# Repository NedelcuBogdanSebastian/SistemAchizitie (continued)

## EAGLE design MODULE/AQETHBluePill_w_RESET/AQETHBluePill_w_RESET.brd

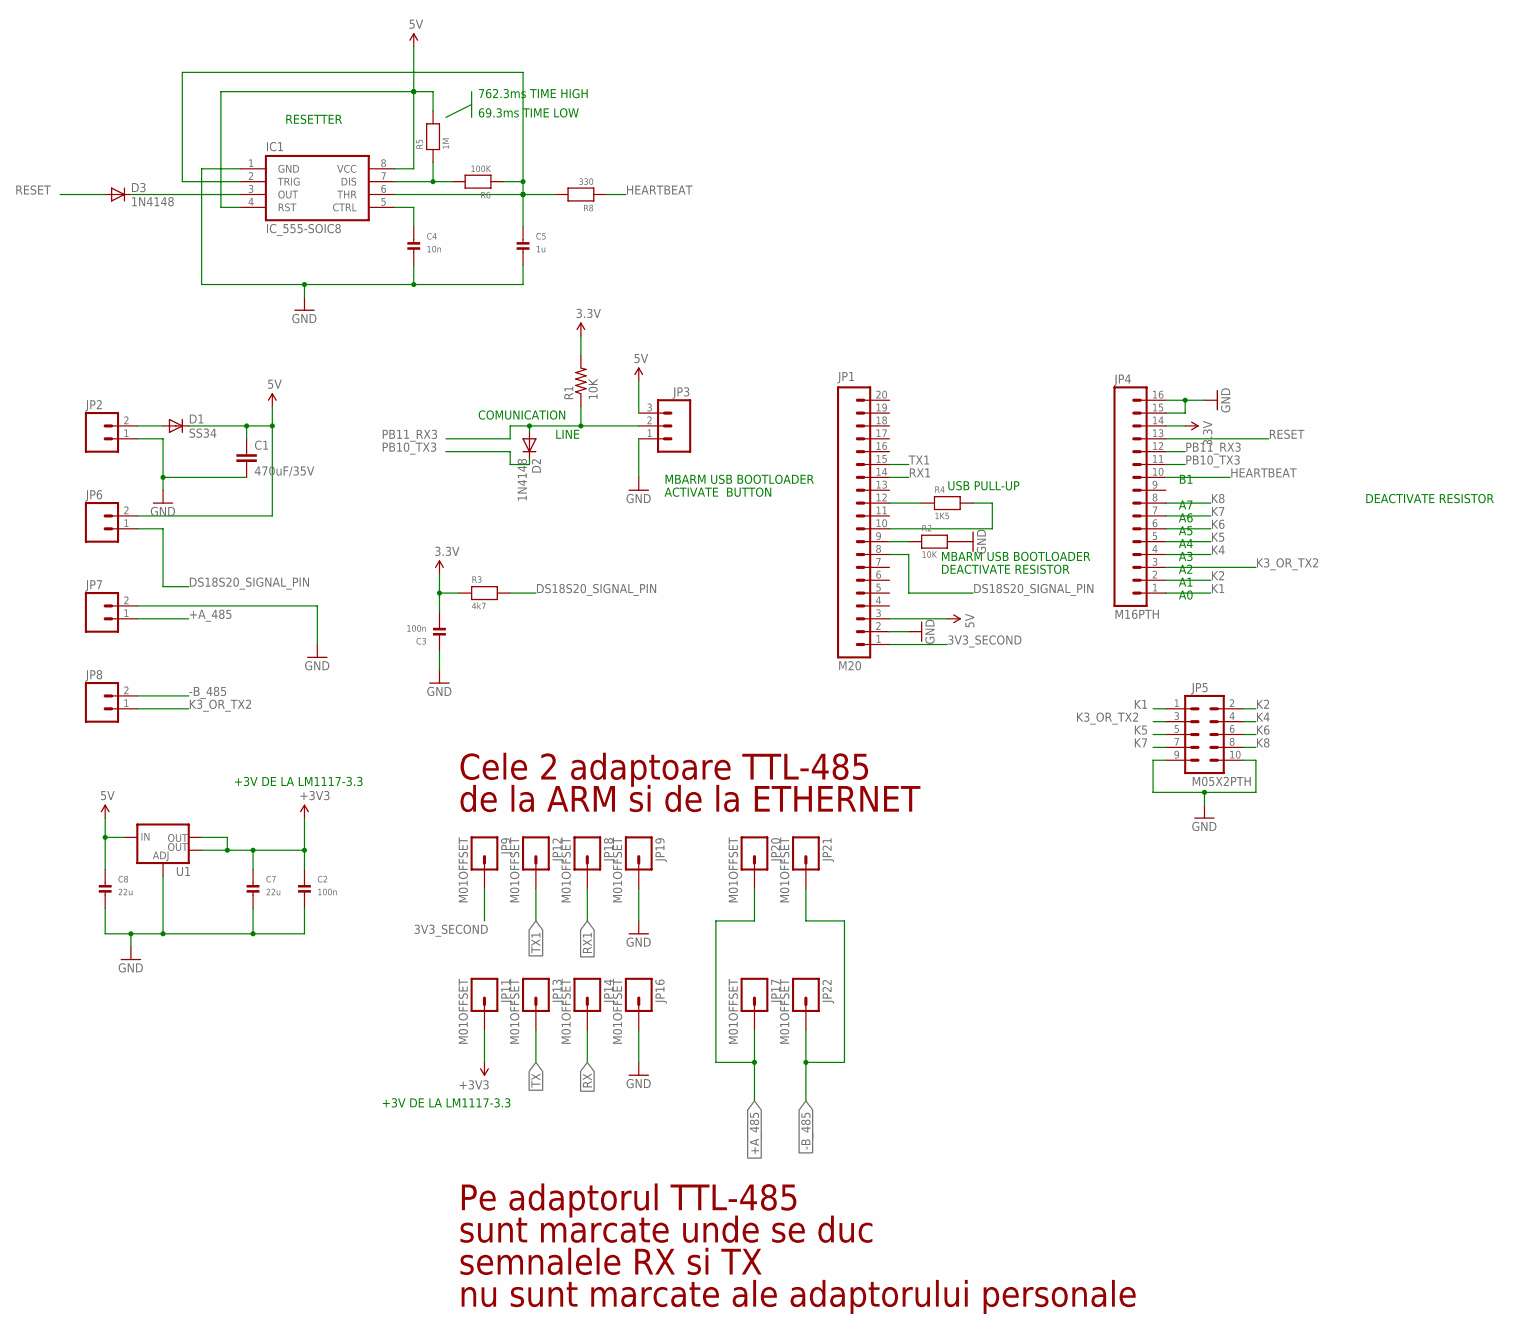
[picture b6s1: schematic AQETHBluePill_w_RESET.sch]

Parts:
C1: 470uF/35V; CAP-PTH-5MM
C2, C3: 100n; _0805MP
C4: 10n; _0805MP
C5: 1u; 1206
C7, C8: 22u; 1206
D1: SS34; SMC
D2, D3: 1N4148; MINIMELF
IC1: IC_555-SOIC8; SOIC-8
JP1: M20; 1X20
JP2, JP6, JP7, JP8: M025MM; SCREWTERMINAL-5MM-2
JP3: M03LOCK_LONGPADS; 1X03_LOCK_LONGPADS
JP4: M16PTH; 1X16
JP5: M05X2PTH; AVR_ICSP
JP9, JP11, JP12, JP13, JP14, JP16, JP17, JP18, JP19, JP20, JP21, JP22: M01OFFSET; 1X01_OFFSET
R1: 10K; 1206
R2: 10K; _0805MP
R3: 4k7; _0805MP
R4: 1K5; _0805MP
R5: 1M; _0805MP
R6: 100K; _0805MP
R8: 330; _0805MP
U1: V_REG_LM1117SOT223; SOT223

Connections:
3.3V: C3.2, JP4.14, R1.2, R3.1
3V3_SECOND: JP1.1, JP9.1
5V: C1.1, C8.1, D1.C, IC1.4 (RST), IC1.8 (VCC), JP1.3, JP3.3, JP6.2, R5.2, U1.3 (IN)
+A_485: JP7.1, JP17.1, JP20.1
-B_485: JP8.2, JP21.1, JP22.1
CTRL: C4.1, IC1.5 (CTRL)
DS18S20_SIGNAL_PIN: JP1.8, JP6.1, R3.2
GND: C1.2, C2.2, C3.1, C4.2, C5.2, C7.2, C8.2, IC1.1 (GND), JP1.2, JP2.1, JP3.1, JP4.15, JP4.16, JP5.9, JP5.10, JP7.2, JP16.1, JP19.1, R2.2, U1.1 (ADJ)
HEARTBEAT: JP4.10, R8.1
K1: JP4.1, JP5.1
K2: JP4.2, JP5.2
K3_OR_TX2: JP4.3, JP5.3, JP8.1
K4: JP4.4, JP5.4
K5: JP4.5, JP5.5
K6: JP4.6, JP5.6
K7: JP4.7, JP5.7
K8: JP4.8, JP5.8
unnamed: JP1.10, R4.2
unnamed: JP1.9, R2.1
unnamed: JP1.12, R4.1
unnamed: C5.1, IC1.2 (TRIG), IC1.6 (THR), R6.1, R8.2
unnamed: D3.C, IC1.3 (OUT)
unnamed: IC1.7 (DIS), R5.1, R6.2
unnamed: D1.A, JP2.2
PB10_TX3: D2.C, JP4.11
PB11_RX3: D2.A, JP3.2, JP4.12, R1.1
RESET: D3.A, JP4.13
RX: JP14.1
RX1: JP1.14, JP18.1
TX: JP13.1
TX1: JP1.15, JP12.1
VCC: C2.1, C7.1, JP11.1, U1.2 (OUT), U1.4 (OUT)

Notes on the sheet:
COMUNICATION
LINE
Pe adaptorul TTL-485
sunt marcate unde se duc
semnalele RX si TX
nu sunt marcate ale adaptorului personale
+3V DE LA LM1117-3.3
Cele 2 adaptoare TTL-485
de la ARM si de la ETHERNET
USB PULL-UP
MBARM USB BOOTLOADER
DEACTIVATE RESISTOR
ACTIVATE BUTTON
69.3ms TIME LOW
762.3ms TIME HIGH
RESETTER

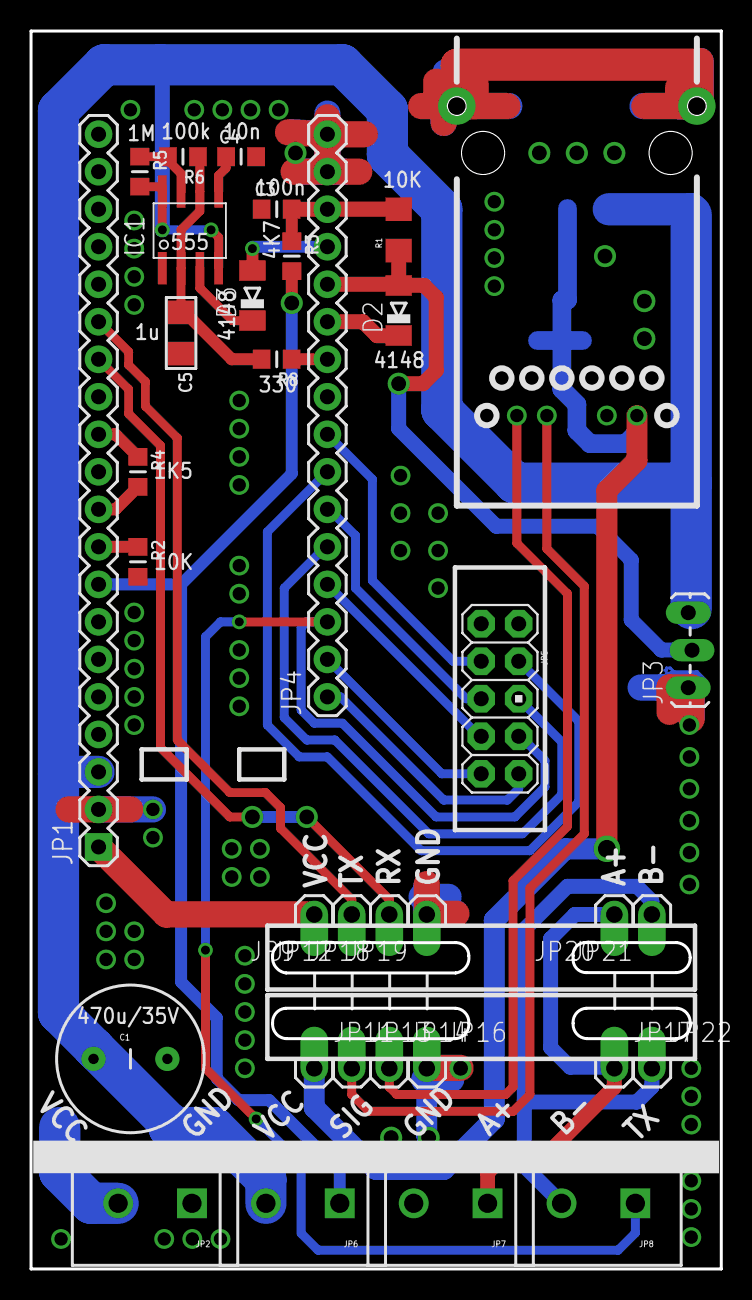
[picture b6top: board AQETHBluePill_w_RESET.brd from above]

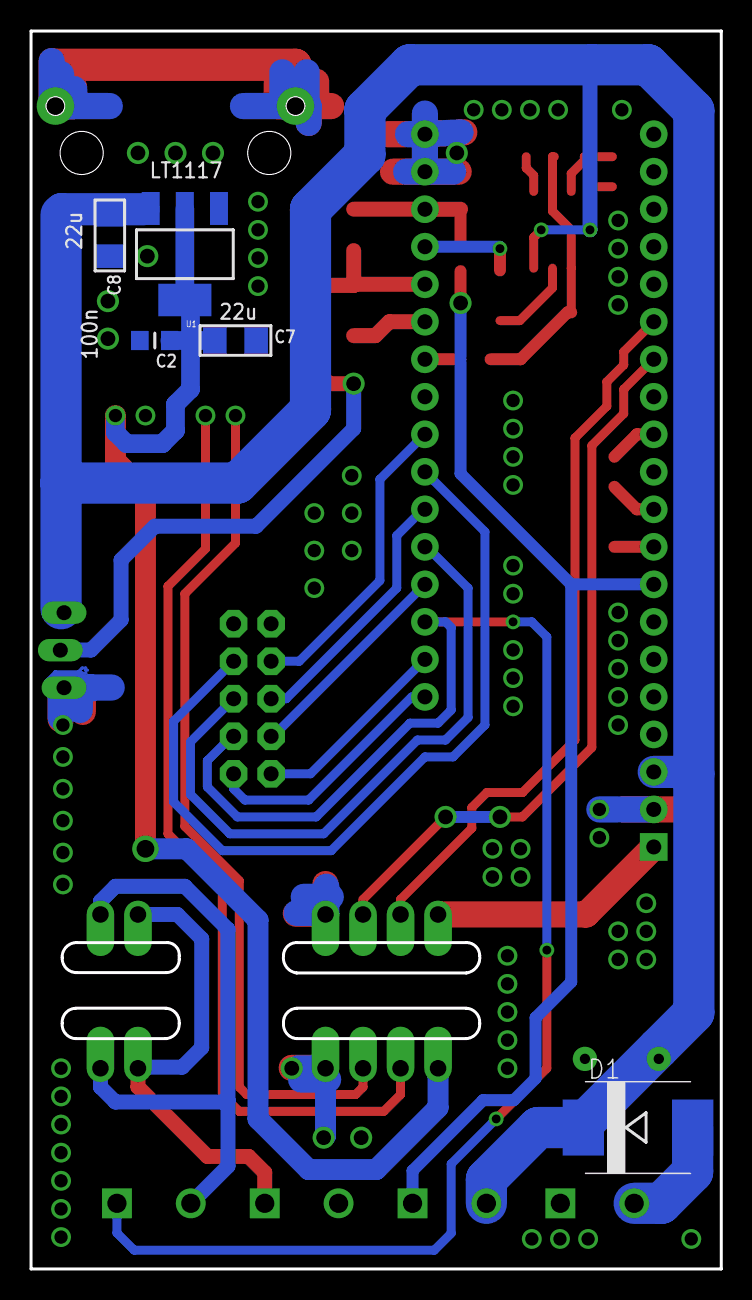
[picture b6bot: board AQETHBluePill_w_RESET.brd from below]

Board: 2 copper layers, 46.7 x 83.8 mm, 39 parts (5 on the bottom side), 30 nets.

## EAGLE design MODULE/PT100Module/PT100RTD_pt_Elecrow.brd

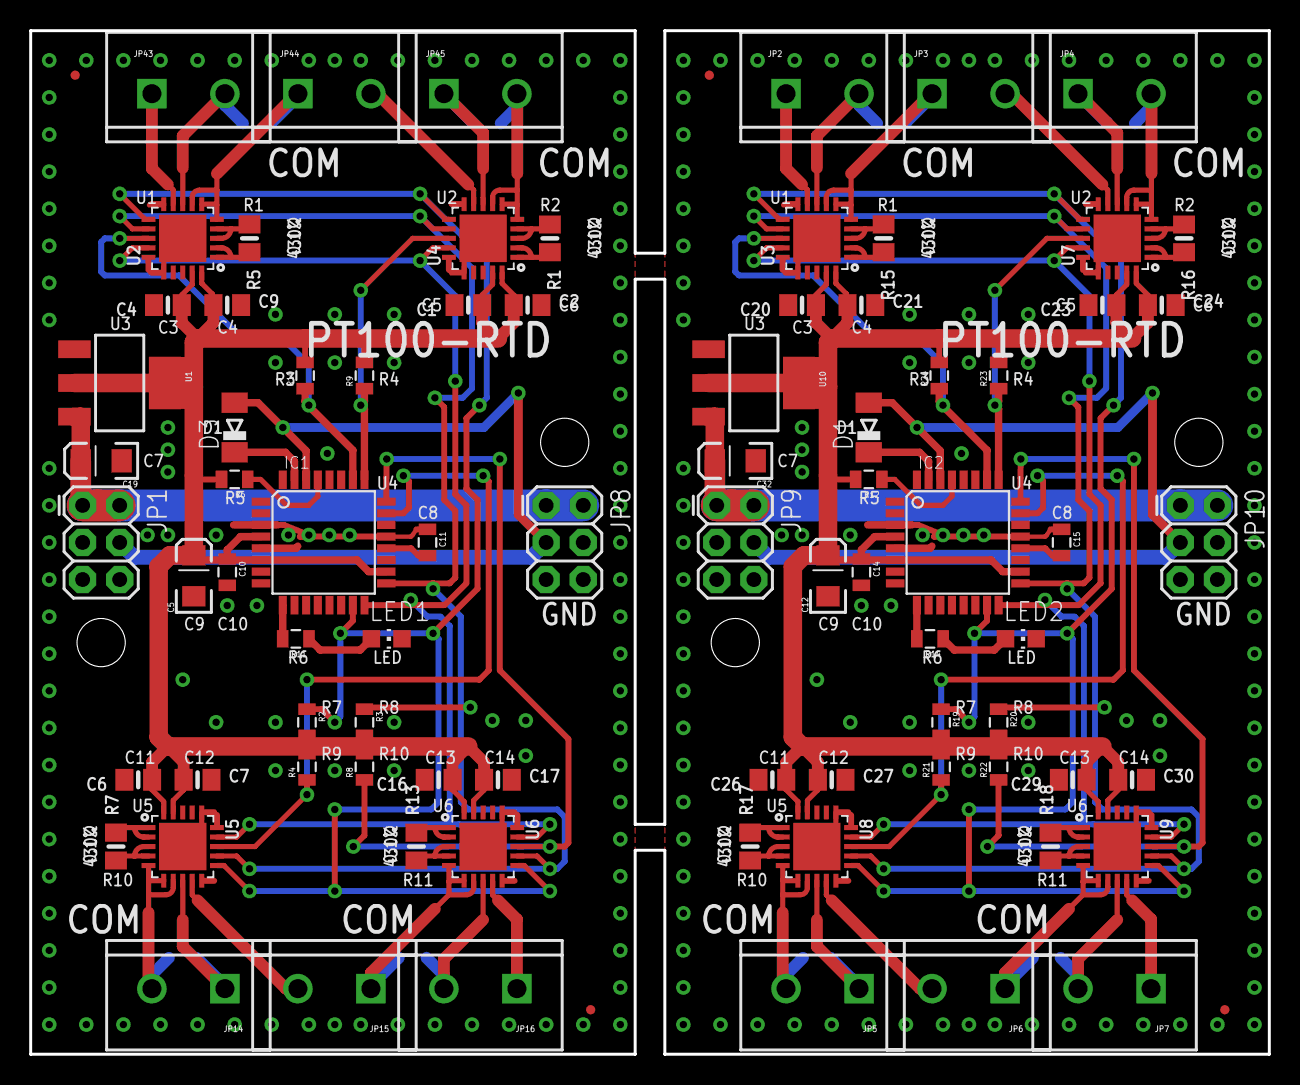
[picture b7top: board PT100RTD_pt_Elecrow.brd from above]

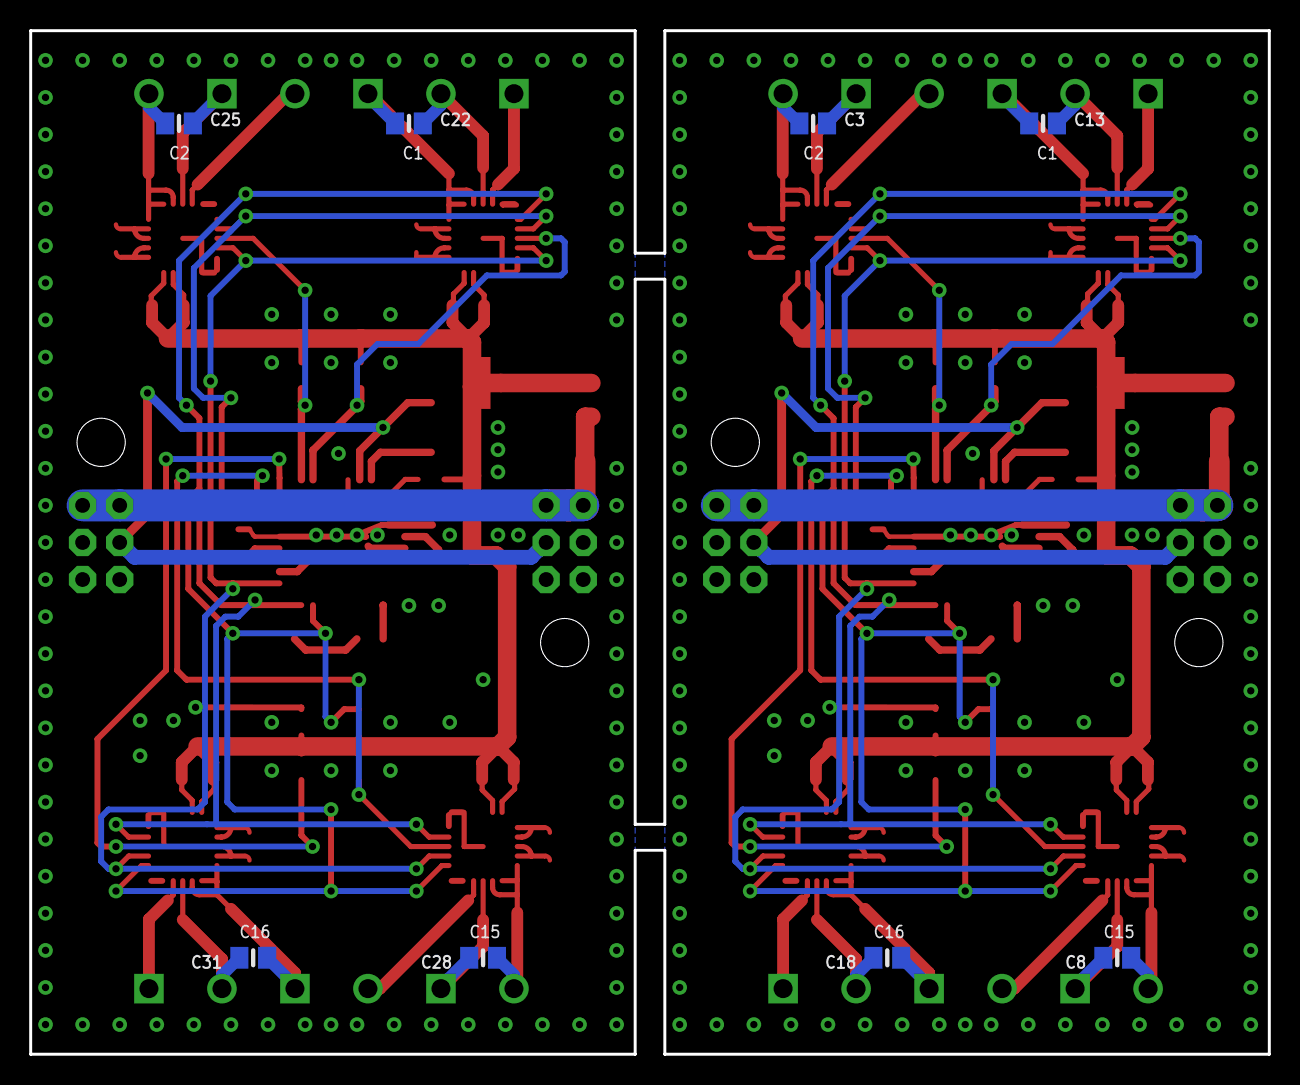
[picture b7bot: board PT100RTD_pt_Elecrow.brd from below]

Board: 2 copper layers, 84.8 x 70.1 mm, 96 parts (8 on the bottom side), 72 nets.

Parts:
C1, C2, C4, C6, C7, C9, C16, C17, C20, C21, C23, C24, C26, C27, C29, C30: 0.1uF; 0805-NO
C3, C8, C13, C18, C22, C25, C28, C31: 100nF; 0805-NO
C5, C12, C19, C32: 22uF/16V; EIA3216
C10, C11, C14, C15: 100n; 0805
D1, D3: 1N4148; MINIMELF
FD1, FD2, FD3, FD4: FIDUCIALUFIDUCIAL; FIDUCIAL-MICRO
IC1, IC2: MEGA8-AI; TQFP32-08
JP1, JP8, JP9, JP10: 2X3
JP2, JP3, JP4, JP5, JP6, JP7, JP14, JP15, JP16, JP43, JP44, JP45: SCREWTERMINAL-5MM-2
LED1, LED2: CHIP-LED0805
R1, R5, R7, R13, R15, R16, R17, R18: 430Ω/0.1%; 0805-NO
R2, R3, R4, R6, R8, R9, R10, R12, R19, R20, R21, R22, R23, R24: 10K; 0805
R11, R14: 0805
STANDOFF1, STANDOFF2, STANDOFF3, STANDOFF4: STAND-OFF
U1, U10: SOT223
U2, U3, U4, U5, U6, U7, U8, U9: MAX31865; QFN20_4MM_0.65MM

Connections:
5V: C19.A, JP1.1, JP1.2, JP8.1, JP8.2, U1.3
5V1: C32.A, JP9.1, JP9.2, JP10.1, JP10.2, U10.3
COM1: D3.A, IC1.30, JP1.4, JP8.3
COM2: D1.A, IC2.30, JP9.4, JP10.3
CS1: IC1.26, R10.1, U2.13
CS2: IC1.25, R9.1, U4.13
CS3: IC1.23, R4.1, U5.13
CS4: IC1.24, R8.1, U6.13
CS5: IC2.26, R24.1, U3.13
CS6: IC2.25, R23.1, U7.13
CS7: IC2.23, R21.1, U8.13
CS8: IC2.24, R22.1, U9.13
GND: C1.2, C2.2, C4.2, C5.C, C6.2, C7.2, C9.2, C10.2, C11.1, C16.2, C17.2, C19.C, IC1.3, IC1.5, IC1.21, JP1.5, JP1.6, JP8.5, JP8.6, LED1.C, U1.1, U2.10, U2.15, U2.16, U2.PAD, U4.10, U4.15, U4.16, U4.PAD, U5.10, U5.15, U5.16, U5.PAD, U6.10, U6.15, U6.16, U6.PAD
GND4: C12.C, C14.2, C15.1, C20.2, C21.2, C23.2, C24.2, C26.2, C27.2, C29.2, C30.2, C32.C, IC2.3, IC2.5, IC2.21, JP9.5, JP9.6, JP10.5, JP10.6, LED2.C, U3.10, U3.15, U3.16, U3.PAD, U7.10, U7.15, U7.16, U7.PAD, U8.10, U8.15, U8.16, U8.PAD, U9.10, U9.15, U9.16, U9.PAD, U10.1
MISO: IC1.16, U2.14, U4.14, U5.14, U6.14
MISO1: IC2.16, U3.14, U7.14, U8.14, U9.14
MOSI: IC1.15, R2.1, U2.11, U4.11, U5.11, U6.11
MOSI1: IC2.15, R19.1, U3.11, U7.11, U8.11, U9.11
unnamed: LED1.A, R11.1
unnamed: D3.C, IC1.31
unnamed: R5.2, U2.1, U2.2
unnamed: R5.1, U2.3, U2.4
unnamed: C11.2, IC1.20
unnamed: R1.2, U4.1, U4.2
unnamed: R1.1, U4.3, U4.4
unnamed: C15.2, IC2.20
unnamed: R7.2, U5.1, U5.2
unnamed: R7.1, U5.3, U5.4
unnamed: IC1.9, R11.2
unnamed: LED2.A, R14.1
unnamed: R13.2, U6.1, U6.2
unnamed: R13.1, U6.3, U6.4
unnamed: D1.C, IC2.31
unnamed: R15.2, U3.1, U3.2
unnamed: R15.1, U3.3, U3.4
unnamed: R16.2, U7.1, U7.2
unnamed: R16.1, U7.3, U7.4
unnamed: R17.2, U8.1, U8.2
unnamed: R17.1, U8.3, U8.4
unnamed: R18.2, U9.1, U9.2
unnamed: R18.1, U9.3, U9.4
unnamed: IC2.9, R14.2
RESET: IC1.29, R6.1
RESET1: IC2.29, R12.1
SCK: IC1.17, R3.1, U2.12, U4.12, U5.12, U6.12
SCK1: IC2.17, R20.1, U3.12, U7.12, U8.12, U9.12
T1A: C13.1, JP44.1, U2.5, U2.6, U2.7
T1A1: C22.1, JP3.1, U3.5, U3.6, U3.7
T1B: C13.2, JP43.2, U2.8
T1B1: C22.2, JP2.2, U3.8
T1C: JP43.1, U2.9
T1C1: JP2.1, U3.9
T2A: C3.1, JP45.2, U4.5, U4.6, U4.7
T2A1: C25.1, JP4.2, U7.5, U7.6, U7.7
T2B: C3.2, JP45.1, U4.8
T2B1: C25.2, JP4.1, U7.8
T2C: JP44.2, U4.9
T2C1: JP3.2, U7.9
T3A: C8.1, JP14.2, U5.5, U5.6, U5.7
T3A1: C28.1, JP5.2, U8.5, U8.6, U8.7
T3B: C8.2, JP14.1, U5.8
T3B1: C28.2, JP5.1, U8.8
T3C: JP15.2, U5.9
T3C1: JP6.2, U8.9
T4A: C18.1, JP15.1, U6.5, U6.6, U6.7
T4A1: C31.1, JP6.1, U9.5, U9.6, U9.7
T4B: C18.2, JP16.2, U6.8
T4B1: C31.2, JP7.2, U9.8
T4C: JP16.1, U6.9
T4C1: JP7.1, U9.9
VCC: C1.1, C2.1, C4.1, C5.A, C6.1, C7.1, C9.1, C10.1, C16.1, C17.1, IC1.4, IC1.6, IC1.18, R2.2, R3.2, R4.2, R6.2, R8.2, R9.2, R10.2, U1.2, U1.4, U2.19, U2.20, U4.19, U4.20, U5.19, U5.20, U6.19, U6.20
VCC1: C12.A, C14.1, C20.1, C21.1, C23.1, C24.1, C26.1, C27.1, C29.1, C30.1, IC2.4, IC2.6, IC2.18, R12.2, R19.2, R20.2, R21.2, R22.2, R23.2, R24.2, U3.19, U3.20, U7.19, U7.20, U8.19, U8.20, U9.19, U9.20, U10.2, U10.4

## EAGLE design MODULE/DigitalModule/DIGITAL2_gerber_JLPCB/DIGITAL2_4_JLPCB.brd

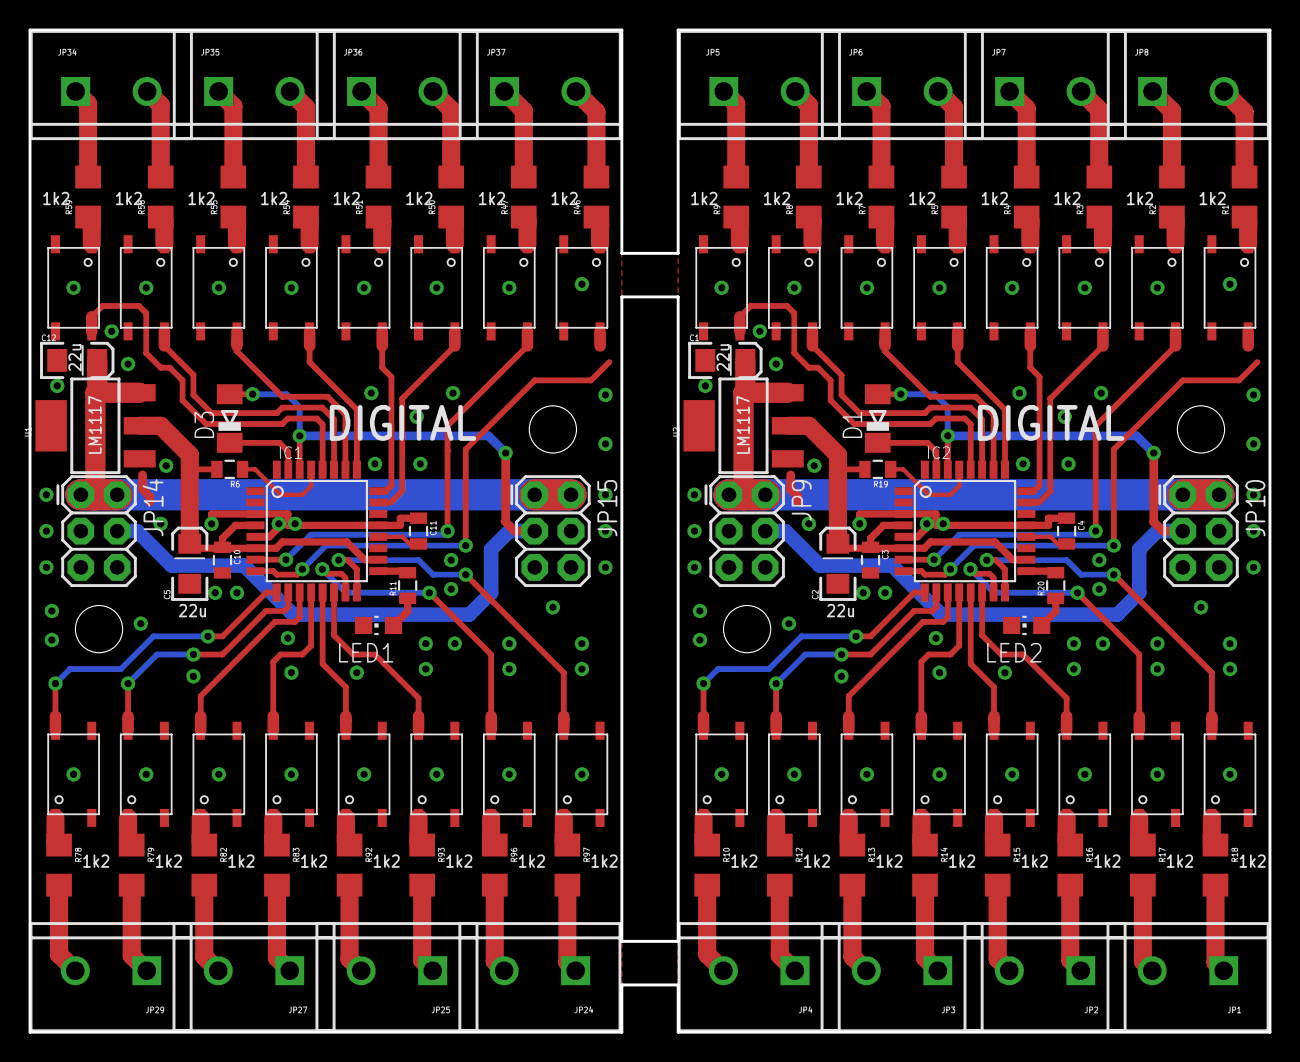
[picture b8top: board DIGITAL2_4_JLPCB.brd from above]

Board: 2 copper layers, 86.7 x 70.1 mm, 108 parts (0 on the bottom side), 114 nets.

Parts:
C1, C2, C5, C12: 22uF/16V; EIA3216
C3, C4, C10, C11: 100n; 0805
D1, D3: 1N4148; MINIMELF
IC1, IC2: MEGA8-AI; TQFP32-08
JP1, JP2, JP3, JP4, JP5, JP6, JP7, JP8, JP24, JP25, JP27, JP29, JP34, JP35, JP36, JP37: SCREWTERMINAL-5MM-2
JP9, JP10, JP14, JP15: 2X3
LED1, LED2: CHIP-LED0805
R1, R2, R3, R4, R5, R7, R8, R9, R10, R12, R13, R14, R15, R16, R17, R18, R46, R47, R50, R51, R54, R55, R58, R59, R78, R79, R82, R83, R92, R93, R96, R97: 1.2K; 1206
R6, R19: 10K; 0805
R11, R20: 0805
STANDOFF1, STANDOFF2, STANDOFF3, STANDOFF4: STAND-OFF
U1, U2: SOT223
U$1, U$2, U$3, U$4, U$5, U$6, U$7, U$8, U$9, U$10, U$11, U$12, U$13, U$14, U$15, U$16, U$17, U$18, U$19, U$20, U$21, U$22, U$23, U$24, U$29, U$30, U$31, U$32, U$33, U$34, U$35, U$36: IS181D-I; TLP181-I

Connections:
5V: C12.A, JP14.1, JP14.2, JP15.1, JP15.2, U1.3
5V1: C1.A, JP9.1, JP9.2, JP10.1, JP10.2, U2.3
COM1: D3.A, IC1.30, JP14.4, JP15.3
COM3: D1.A, IC2.30, JP9.4, JP10.3
D1: IC2.9, U$9.P$4
D2: IC2.10, U$10.P$4
D3: IC1.8, U$13.P$4
D4: IC1.7, U$14.P$4
D5: IC1.23, U$15.P$4
D6: IC1.24, U$16.P$4
D7: IC1.25, U$17.P$4
D8: IC1.26, U$18.P$4
D9: IC1.27, U$19.P$4
D10: IC1.28, U$20.P$4
D11: IC1.9, U$29.P$4
D12: IC1.10, U$30.P$4
D13: IC1.11, U$31.P$4
D14: IC1.12, U$32.P$4
D15: IC1.13, U$33.P$4
D16: IC1.14, U$34.P$4
D17: IC1.15, U$35.P$4
D18: IC1.16, U$36.P$4
D19: IC2.11, U$11.P$4
D20: IC2.12, U$12.P$4
D21: IC2.13, U$21.P$4
D22: IC2.14, U$22.P$4
D23: IC2.15, U$23.P$4
D24: IC2.16, U$24.P$4
D25: IC2.8, U$1.P$4
D26: IC2.7, U$2.P$4
D27: IC2.23, U$3.P$4
D28: IC2.24, U$4.P$4
D29: IC2.25, U$5.P$4
D30: IC2.26, U$6.P$4
D31: IC2.27, U$7.P$4
D32: IC2.28, U$8.P$4
GND: C5.C, C10.2, C11.1, C12.C, IC1.3, IC1.5, IC1.21, JP14.5, JP14.6, JP15.5, JP15.6, LED1.C, U1.1, U$13.P$2, U$13.P$3, U$14.P$2, U$14.P$3, U$15.P$2, U$15.P$3, U$16.P$2, U$16.P$3, U$17.P$2, U$17.P$3, U$18.P$2, U$18.P$3, U$19.P$2, U$19.P$3, U$20.P$2, U$20.P$3, U$29.P$2, U$29.P$3, U$30.P$2, U$30.P$3, U$31.P$2, U$31.P$3, U$32.P$2, U$32.P$3, U$33.P$2, U$33.P$3, U$34.P$2, U$34.P$3, U$35.P$2, U$35.P$3, U$36.P$2, U$36.P$3
GND2: C1.C, C2.C, C3.2, C4.1, IC2.3, IC2.5, IC2.21, JP9.5, JP9.6, JP10.5, JP10.6, LED2.C, U2.1, U$1.P$2, U$1.P$3, U$2.P$2, U$2.P$3, U$3.P$2, U$3.P$3, U$4.P$2, U$4.P$3, U$5.P$2, U$5.P$3, U$6.P$2, U$6.P$3, U$7.P$2, U$7.P$3, U$8.P$2, U$8.P$3, U$9.P$2, U$9.P$3, U$10.P$2, U$10.P$3, U$11.P$2, U$11.P$3, U$12.P$2, U$12.P$3, U$21.P$2, U$21.P$3, U$22.P$2, U$22.P$3, U$23.P$2, U$23.P$3, U$24.P$2, U$24.P$3
unnamed: LED1.A, R11.1
unnamed: JP8.2, R1.2
unnamed: D3.C, IC1.31
unnamed: JP29.2, R78.2
unnamed: C11.2, IC1.20
unnamed: JP27.2, R82.2
unnamed: JP25.2, R92.2
unnamed: JP8.1, R2.2
unnamed: R1.1, U$1.P$1
unnamed: R2.1, U$2.P$1
unnamed: JP24.2, R96.2
unnamed: JP7.2, R3.2
unnamed: JP7.1, R4.2
unnamed: R3.1, U$3.P$1
unnamed: R4.1, U$4.P$1
unnamed: JP6.2, R5.2
unnamed: JP6.1, R7.2
unnamed: R5.1, U$5.P$1
unnamed: R7.1, U$6.P$1
unnamed: JP27.1, R83.2
unnamed: JP5.2, R8.2
unnamed: JP5.1, R9.2
unnamed: JP25.1, R93.2
unnamed: R8.1, U$7.P$1
unnamed: R9.1, U$8.P$1
unnamed: JP4.1, R12.2
unnamed: R10.1, U$9.P$1
unnamed: JP24.1, R97.2
unnamed: R12.1, U$10.P$1
unnamed: R13.1, U$11.P$1
unnamed: R14.1, U$12.P$1
unnamed: R15.1, U$21.P$1
unnamed: R16.1, U$22.P$1
unnamed: R17.1, U$23.P$1
unnamed: R18.1, U$24.P$1
unnamed: JP3.1, R14.2
unnamed: JP2.1, R16.2
unnamed: JP1.1, R18.2
unnamed: JP4.2, R10.2
unnamed: JP3.2, R13.2
unnamed: JP2.2, R15.2
unnamed: JP1.2, R17.2
unnamed: C4.2, IC2.20
unnamed: LED2.A, R20.1
unnamed: D1.C, IC2.31
unnamed: JP37.2, R46.2
unnamed: JP37.1, R47.2
unnamed: R46.1, U$13.P$1
unnamed: R47.1, U$14.P$1
unnamed: JP36.2, R50.2
unnamed: JP36.1, R51.2
unnamed: R50.1, U$15.P$1
unnamed: R51.1, U$16.P$1
unnamed: JP35.2, R54.2
unnamed: JP35.1, R55.2
unnamed: R54.1, U$17.P$1
unnamed: R55.1, U$18.P$1
unnamed: JP34.2, R58.2
unnamed: JP34.1, R59.2
unnamed: R58.1, U$19.P$1
unnamed: R59.1, U$20.P$1
unnamed: JP29.1, R79.2
unnamed: R78.1, U$29.P$1
unnamed: R79.1, U$30.P$1
unnamed: R82.1, U$31.P$1
unnamed: R83.1, U$32.P$1
unnamed: R92.1, U$33.P$1
unnamed: R93.1, U$34.P$1
unnamed: R96.1, U$35.P$1
unnamed: R97.1, U$36.P$1
RESET: IC1.29, R6.1
RESET2: IC2.29, R19.1
SCK: IC1.17, R11.2
SCK2: IC2.17, R20.2
VCC: C5.A, C10.1, IC1.4, IC1.6, IC1.18, R6.2, U1.2, U1.4
VCC2: C2.A, C3.1, IC2.4, IC2.6, IC2.18, R19.2, U2.2, U2.4

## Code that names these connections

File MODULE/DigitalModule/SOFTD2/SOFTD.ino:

/*
 * SOFT DIGITALE
 * 
 * FUSES
 * --------
 * EFUSE = 0xff     // = 0x07
 * HFUSE = 0xde
 * LFUSE = 0xe2
 * 
 */
 
#define ID   "DA9"

#define LEDON    PORTB |= (1<<PB5)
#define LEDOFF   PORTB &= ~(1<<PB5)

#define TO_HEX(i)   (i <= 9 ? '0' + i : 'A' - 10 + i)

uint16_t u16CRC;

String str;

/*
CRC Generation from the MODBUS Specification V1.02: 
1. Load a 16bit register with FFFF hex (all 1’s). Call this the CRC register. 
2. Exclusive OR the first 8bit byte of the message with the low order byte of the 16 bit CRC register, putting the result in the 
CRC register. 
3. Shift the CRC register one bit to the right (toward the LSB), zero filling the MSB. 
Extract and examine the LSB. 
4. (If the LSB was 0): Repeat Step 3 (another shift). 
(If the LSB was 1): Exclusive OR the CRC register with the polynomial value 0xA001 (1010 0000 0000 0001). 
5. Repeat Steps 3 and 4 until 8 shifts have been performed. When this is done, a complete 8bit byte will have been processed. 
6. Repeat Steps 2 through 5 for the next 8bit byte of the message. Continue doing this until all bytes have been processed. 
7. The final content of the CRC register is the CRC value. 
8. When the CRC is placed into the message, its upper and lower bytes must be swapped.
*/
uint16_t crc16_update(uint16_t crc, uint8_t a)
{
  int i;

  crc ^= a;
  for (i = 0; i < 8; ++i)
  {
    if (crc & 1)
      crc = (crc >> 1) ^ 0xA001;
    else
      crc = (crc >> 1);
  }

  return crc;
}

void setup() {
  // initialize serial port
  Serial.begin(19200);

  // led pin as output
  DDRB |= (1<<PB5);
  LEDOFF;

  // activate pull-ups 
  PORTB |= (1<<PB7)|(1<<PB6)|(1<<PB4)|(1<<PB3)|(1<<PB2)|(1<<PB1)|(1<<PB0);  
  PORTC |= (1<<PC5)|(1<<PC4)|(1<<PC3)|(1<<PC2)|(1<<PC1)|(1<<PC0);
  PORTD |= (1<<PD7)|(1<<PD6)|(1<<PD5);   

  // initialize pins as input
  DDRB &= ~((1<<PB7)&(1<<PB6)&(1<<PB4)&(1<<PB3)&(1<<PB2)&(1<<PB1)&(1<<PB0));  
  DDRC &= ~((1<<PC5)&(1<<PC4)&(1<<PC3)&(1<<PC2)&(1<<PC1)&(1<<PC0));
  DDRD &= ~((1<<PD7)&(1<<PD6)&(1<<PD5));
   
  for (int i=0; i < 10; i++)
  {
    delay(30);    
    LEDON;
    delay(30);
    LEDOFF;
  }            
}

void loop() 
{
  // if we receive one char then enter this block
  if (Serial.available())
  {    
    // if we have '/' char then proceed processing more incoming chars
    if (Serial.read() == '/')
    {      
      str = "";
      Serial.setTimeout(100);      
      str = Serial.readStringUntil('\\');
      
      unsigned long now = millis ();
      while (millis () - now < 50)
        if (Serial.available())
          Serial.read();  // read and discard any input        
        
      if (str == ID) send_inputs();      
    }
  }
}

uint8_t b2c(uint8_t nr)
{
  if (nr == 0)
      return 1;
  else
      return 0;
}

void send_inputs(void)
{
  uint8_t octet, a, b, c, d;
  char buf[30];  
  
  LEDON;

  unsigned long now = millis();

  uint8_t i = 0;
  buf[i++] = ';';
 
  // top side
  
  a = b2c(PINC & (1<<PC5));
  b = b2c(PINC & (1<<PC4));
  c = b2c(PINC & (1<<PC3));
  d = b2c(PINC & (1<<PC2));
  octet = (a<<3)|(b<<2)|(c<<1)|(d<<0);  
  buf[i++] = TO_HEX(octet);

  a = b2c(PINC & (1<<PC1));
  b = b2c(PINC & (1<<PC0));
  c = b2c(PINB & (1<<PB6));
  d = b2c(PINB & (1<<PB7));
  octet = (a<<3)|(b<<2)|(c<<1)|(d<<0);  
  buf[i++] = TO_HEX(octet);

  // bottom side

  a =  b2c(PIND & (1<<PD5));
  b =  b2c(PIND & (1<<PD6));
  c =  b2c(PIND & (1<<PD7));
  d =  b2c(PINB & (1<<PB0));
  octet = (a<<3)|(b<<2)|(c<<1)|(d<<0);  
  buf[i++] = TO_HEX(octet);
  
  a = b2c(PINB & (1<<PB1));
  b = b2c(PINB & (1<<PB2));
  c = b2c(PINB & (1<<PB3));
  d = b2c(PINB & (1<<PB4));
  octet = (a<<3)|(b<<2)|(c<<1)|(d<<0);  
  buf[i++] = TO_HEX(octet);

  u16CRC = 0xFFFF;
  for (uint8_t j=0; j<i; j++)
    u16CRC = crc16_update(u16CRC, buf[j]);

  buf[i++] = TO_HEX(((u16CRC & 0xF000) >> 12));
  buf[i++] = TO_HEX(((u16CRC & 0x0F00) >> 8));
  buf[i++] = TO_HEX(((u16CRC & 0x00F0) >> 4));
  buf[i++] = TO_HEX( (u16CRC & 0x000F));

  buf[i++] = '?';
    
  buf[i++] = 0;   // string ending
  
  Serial.print((char*)buf);

  // wait at least 12 ms
  while (millis() - now < 12);
  
  LEDOFF;   
}
